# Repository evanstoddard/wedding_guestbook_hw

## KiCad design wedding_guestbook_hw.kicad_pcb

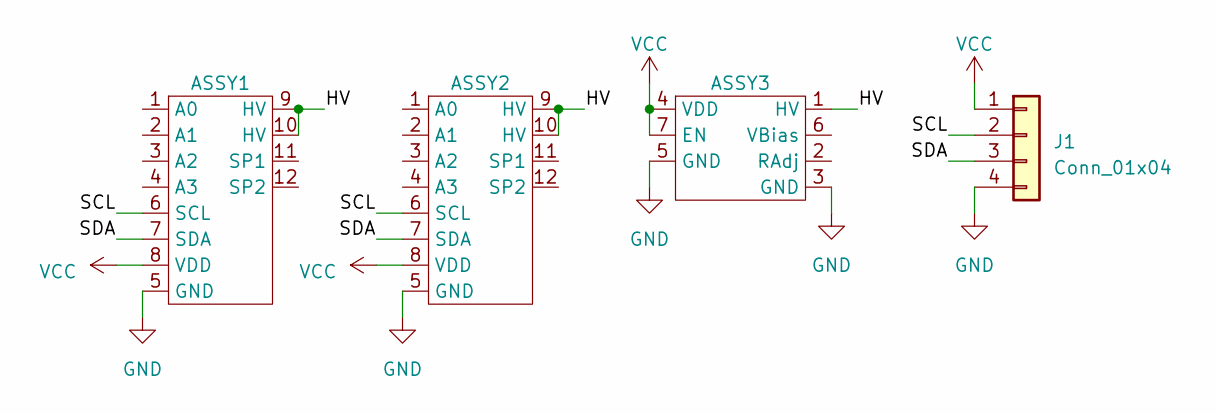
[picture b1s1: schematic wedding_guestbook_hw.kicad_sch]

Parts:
ASSY1, ASSY2: 1356ST
ASSY3: 1364 - HVPS
J1: Conn_01x04; PinHeader_1x04_P2.54mm_Vertical

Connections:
/HV: ASSY1.9 (HV), ASSY1.10 (HV), ASSY2.9 (HV), ASSY2.10 (HV), ASSY3.1 (HV)
/SCL: ASSY1.6 (SCL), ASSY2.6 (SCL), J1.2
/SDA: ASSY1.7 (SDA), ASSY2.7 (SDA), J1.3
GND: ASSY1.5 (GND), ASSY2.5 (GND), ASSY3.3 (GND), ASSY3.5 (GND), J1.4
VCC: ASSY1.8 (VDD), ASSY2.8 (VDD), ASSY3.4 (VDD), ASSY3.7 (EN), J1.1

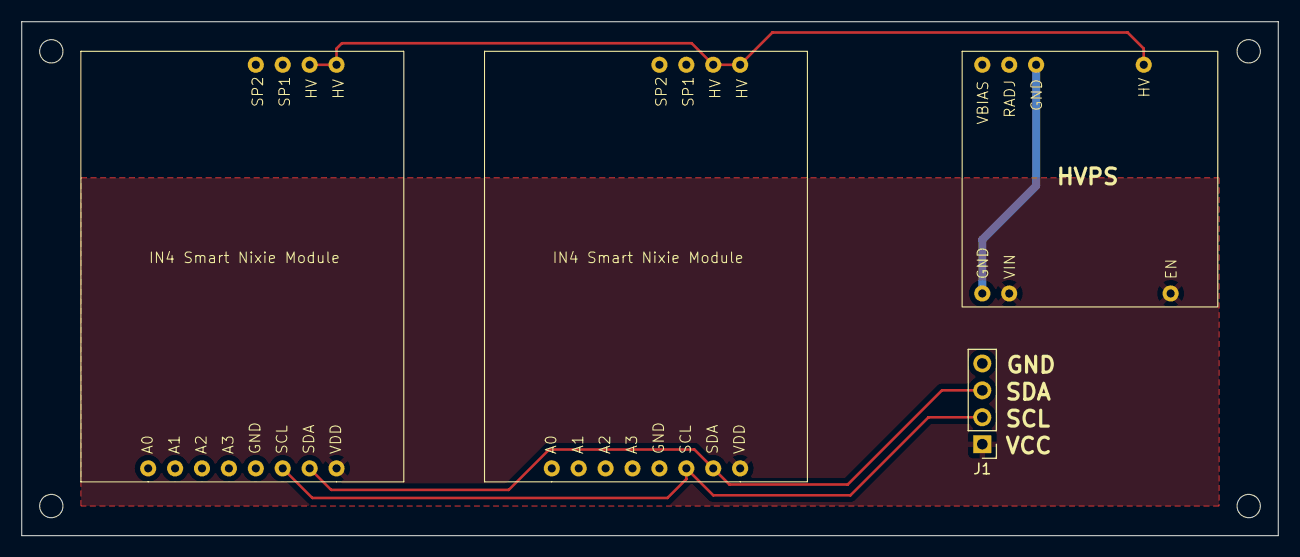
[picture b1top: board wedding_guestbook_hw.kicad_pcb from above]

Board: 2 copper layers, 118.6 x 48.5 mm, 4 parts (0 on the bottom side), 5 nets.

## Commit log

2023-05-06 Fixed pin direction for HV pinx on nixie tube schematic
2023-05-06 Add HVPS schematic symbol
2023-05-06 Added gitignore
2023-05-06 Schematic for nixie tubes
2023-05-06 Added footprint for smart nixie IN4 module.
2023-05-06 Updated IN4 footprint origin
2023-05-06 Added 1364 HVPS footprint
2023-05-06 Updated 1x4 conn footprint assignment
2023-05-06 Created PCB
2023-05-06 Reversed text for bottom layer
